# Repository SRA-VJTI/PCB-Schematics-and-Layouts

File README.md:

# PCB Schematics and Layouts
This Repository contains the schematic and layout files for all the PCBs designed at SRA for various competitions and workshops.

- **Robocon PCBs 2016**  
  PCB files made for the *Manually Operated Robot* in **Robocon 2016**.  
  Designed on **Autodesk EAGLE CAD**.  
  - **128 breakout**  
    - This is the breakout board for the *Atmega 128 Microcontroller* SMD Package.  
    - It also consists the External Clock Circuit and a connector slot for the programmer cable.  
  - **Main Board**  
    - The microcontroller breakout circuit is mounted on this pcb.  
    - It contains peripherals like input switches & LEDs, fuses for short-circuit protection and various connectors to connect sensors & actuators to the controller.  
    
- **Robocon PCBs 2017**  
  PCB files made for the *Manually Operated Robot* in **Robocon 2017**.  
  Designed on **Autodesk EAGLE CAD**.  
  - **128 breakout**  
    - This is the breakout board for the *Atmega 128 Microcontroller* SMD Package.  
    - It also consists the External Clock Circuit and a connector slot for the programmer cable.  
  - **Main Board**  
    - The microcontroller breakout circuit is mounted on this pcb.  
    - It contains peripherals like input switches & LEDs, fuses for short-circuit protection and various connectors to connect sensors & actuators to the controller.  
  - **Line Sensing Array**  
    - It contains a sensor array to detect different colors to help follow a line.  
  - **Power and Motor Control Breakout**  
    - It contains the circuit to connect several motor drivers to a single connector.  
    - It also has a Relay-based braking ciruit to pyhsically short the DC motor terminals.  
    - This PCB also contains the voltage regulators to power the microntroller circuits as well as the motor controllers.  

- **WallE 2016 Dev Brd**  
  - PCB files made for the **Line-follower Robot Workshop (WallE)** in the year 2016.  
  - It uses an **Atmega 16 Microcontroller** in its DIP package, with peripherals like input switches & LEDs, fuses for short-circuit protection, external clock circuit, programmer slot and various connectors to connect sensors & actuators to the controller.  
  - Designed on **KiCAD**.  

- **WallE 2.0 2017 Dev Brd**  
  - PCB files made for the **Line-follower and Self-Balancing Robot Workshop (WallE 2.0)** in the year 2017.  
  - Compared to the 2016 Dev Brd, this iteration has an extra slot to connect an MPU6050 inertial sensor.  
  - Designed on **Autodesk EAGLE CAD**.  

- **MPU Board**  
  - PCB files made for the **MPU 6050** inertial sensor breakout board, used in the **Self-balancing Robot Workshop (WallE 2.0)**.   
  - It has onboard *Pull-up resistors* for the *I2C protocol* lines (SCL and SDA).  
  - Connects to the main Dev Board through a 6 pin Flat Ribbon Cable.  
  - Designed on **Autodesk EAGLE CAD**.  

- **WallE 2.1 2018 Dev Brd**  
  - PCB files made for the **Line-follower and Self-Balancing Robot Workshop (WallE 2.1)** in the year 2018.  
  - It uses an **Espressif System's ESP32** SoC DevKit, with peripherals like input switches & LEDs, fuses for short-circuit protection, external clock circuit and various connectors to connect sensors & actuators to the controller.  
  - Designed on **Autodesk EAGLE CAD**.  

- **ESP 8266 Board**  
  - PCB files made for the **IOT Workshop** in the year 2016.  
  - It uses **Espressif System's ESP 8266** SoC.  
  - Contains a switch to toggle between flash mode and GPIO mode. 
  - Designed on **Autodesk EAGLE CAD**.

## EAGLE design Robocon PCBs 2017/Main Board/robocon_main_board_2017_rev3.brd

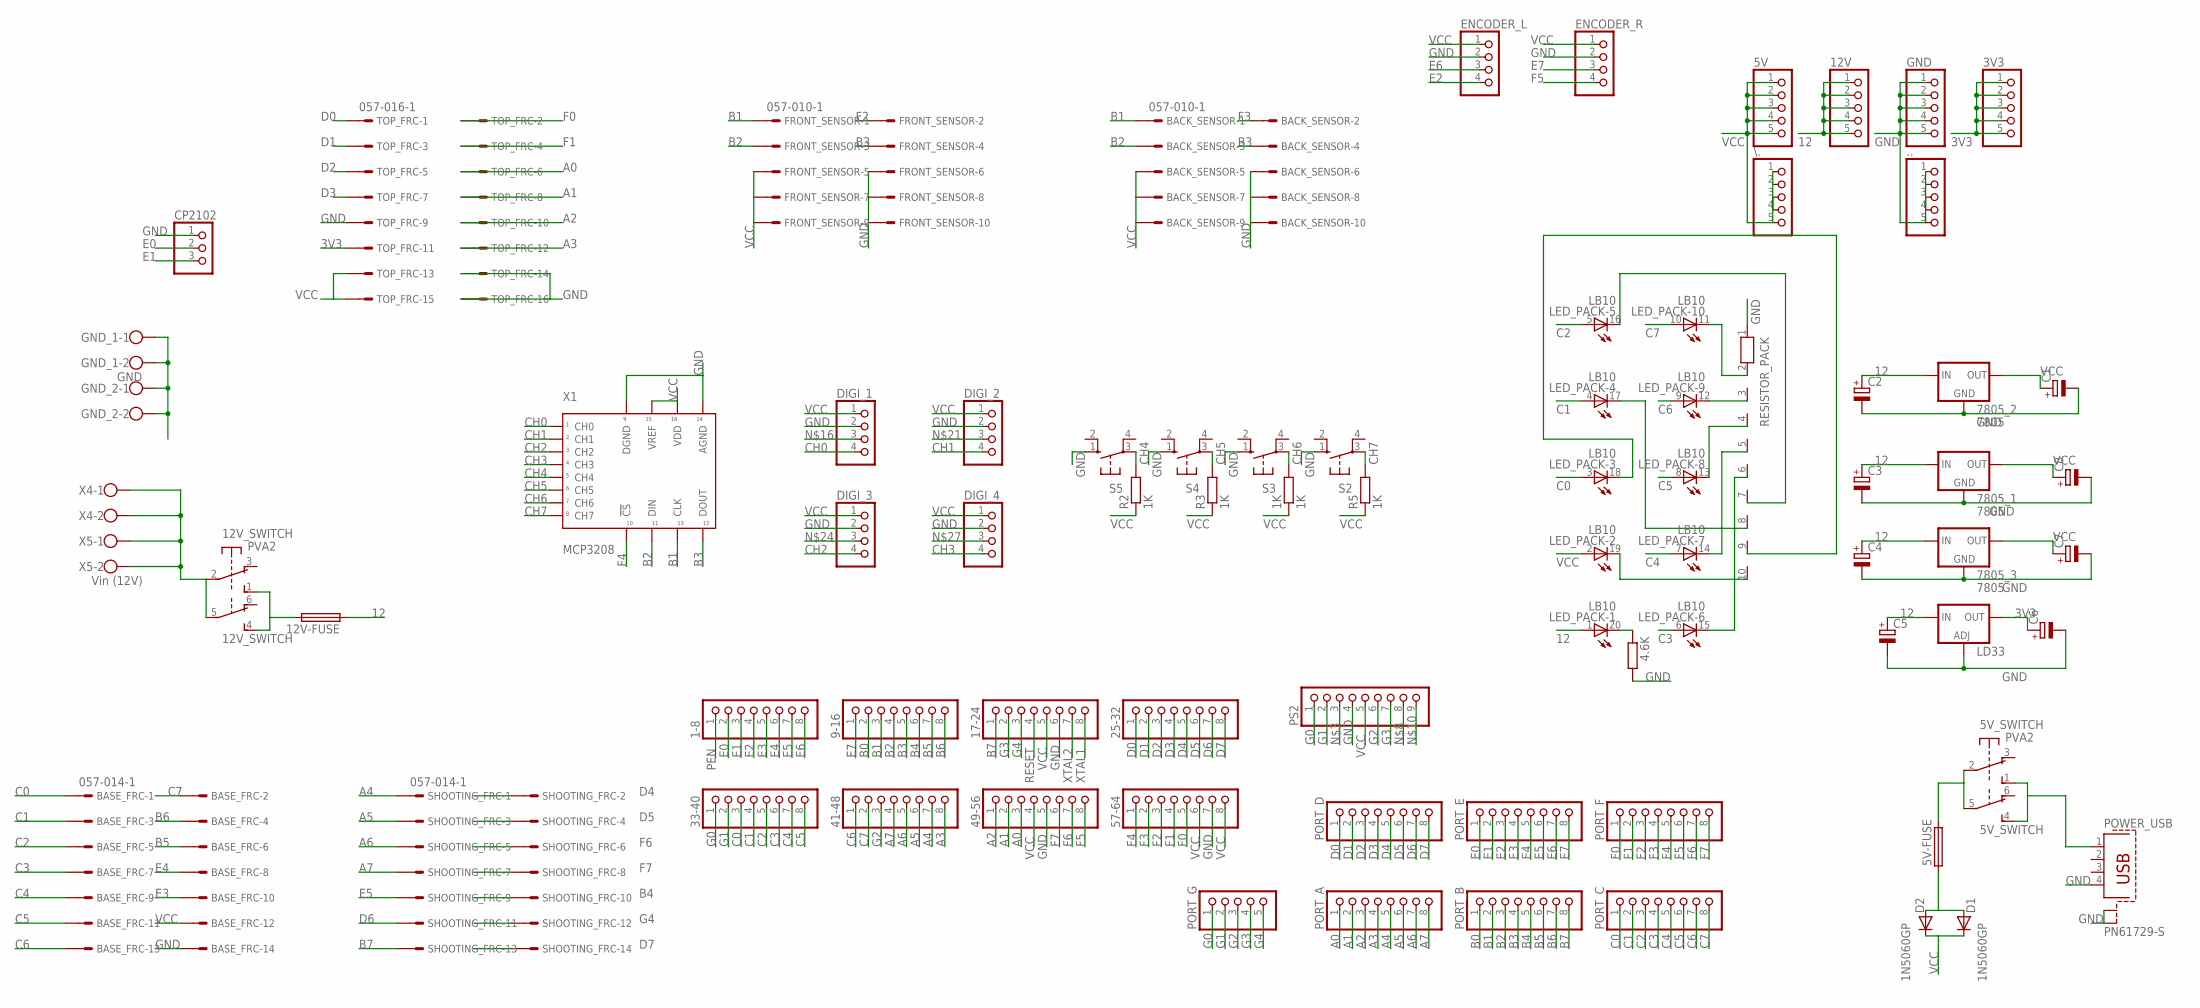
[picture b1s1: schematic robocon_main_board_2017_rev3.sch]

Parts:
1-8, 9-16, 17-24, 25-32, 33-40, 41-48, 49-56, 57-64: PINHD-1X8; 1X08
1K: 1K; 0204/7
3V3, 5V, 12V, ..: PINHD-1X5; 1X05
4.6K: R0204/7; 0204/7
5V-FUSE, 12V-FUSE: SH25
5V_SWITCH, 12V_SWITCH: PVA2; PVA2F
7805_1, 7805_2, 7805_3: 7805; 78XXS
BACK_SENSOR: 057-010-1
BASE_FRC: 057-014-1
C1, C2, C3, C4, C5, C6, C7, C8: CPOL-EUE2.5-5; E2,5-5
CP2102: PINHD-1X3; 1X03
D1, D2: 1N5060GP; DO15-12
DIGI_1, DIGI_2, DIGI_3, DIGI_4: PINHD-1X4; 1X04
ENCODER_L: PINHD-1X4; 1X04
ENCODER_R: PINHD-1X4; 1X04
FRONT_SENSOR: 057-010-1
GND: PINHD-1X5; 1X05
GND_1: GND; W237-102
GND_2: W237-102
LD33: LM317TS; 317TS
LED_PACK: LB10
PORT_A: PINHD-1X8; 1X08
PORT_B: PINHD-1X8; 1X08
PORT_C: PINHD-1X8; 1X08
PORT_D: PINHD-1X8; 1X08
PORT_E: PINHD-1X8; 1X08
PORT_F: PINHD-1X8; 1X08
PORT_G: PINHD-1X5; 1X05
POWER_USB: PN61729-S
PS2: PINHD-1X9; 1X09
R2, R3, R5: 1K; 0204/7
RESISTOR_PACK: RN09; RN-10
S2, S3, S4, S5: 10-XX; B3F-10XX
SHOOTING_FRC: 057-014-1
TOP_FRC: 057-016-1
X1: MCP3208; DIP16
X4: W237-102
X5: Vin (12V); W237-102
\.: PINHD-1X5; 1X05

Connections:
3V3: 3V3.1, 3V3.2, 3V3.3, 3V3.4, 3V3.5, C6.+, LD33.2 (OUT), TOP_FRC.11
12: 12V.1, 12V.2, 12V.3, 12V.4, 12V.5, 12V-FUSE.1, 7805_1.IN, 7805_2.IN, 7805_3.IN, C2.+, C3.+, C4.+, C5.+, LD33.3 (IN), LED_PACK.1 (A)
A0: 49-56.3, PORT_A.1, TOP_FRC.6
A1: 49-56.2, PORT_A.2, TOP_FRC.8
A2: 49-56.1, PORT_A.3, TOP_FRC.10
A3: 41-48.8, PORT_A.4, TOP_FRC.12
A4: 41-48.7, PORT_A.5, SHOOTING_FRC.1
A5: 41-48.6, PORT_A.6, SHOOTING_FRC.3
A6: 41-48.5, PORT_A.7, SHOOTING_FRC.5
A7: 41-48.4, PORT_A.8, SHOOTING_FRC.7
B0: 9-16.2, PORT_B.1
B1: 9-16.3, BACK_SENSOR.1, FRONT_SENSOR.1, PORT_B.2, X1.P$13 (CLK)
B2: 9-16.4, BACK_SENSOR.3, FRONT_SENSOR.3, PORT_B.3, X1.P$11 (DIN)
B3: 9-16.5, BACK_SENSOR.4, FRONT_SENSOR.4, PORT_B.4, X1.P$12 (DOUT)
B4: 9-16.6, PORT_B.5, SHOOTING_FRC.10
B5: 9-16.7, BASE_FRC.6, PORT_B.6
B6: 9-16.8, BASE_FRC.4, PORT_B.7
B7: 17-24.1, PORT_B.8, SHOOTING_FRC.13
C0: 33-40.3, BASE_FRC.1, LED_PACK.3 (A), PORT_C.1
C1: 33-40.4, BASE_FRC.3, LED_PACK.4 (A), PORT_C.2
C2: 33-40.5, BASE_FRC.5, LED_PACK.5 (A), PORT_C.3
C3: 33-40.6, BASE_FRC.7, LED_PACK.6 (A), PORT_C.4
C4: 33-40.7, BASE_FRC.9, LED_PACK.7 (A), PORT_C.5
C5: 33-40.8, BASE_FRC.11, LED_PACK.8 (A), PORT_C.6
C6: 41-48.1, BASE_FRC.13, LED_PACK.9 (A), PORT_C.7
C7: 41-48.2, BASE_FRC.2, LED_PACK.10 (A), PORT_C.8
CH0: DIGI_1.4, X1.P$1 (CH0)
CH1: DIGI_2.4, X1.P$2 (CH1)
CH2: DIGI_3.4, X1.P$3 (CH2)
CH3: DIGI_4.4, X1.P$4 (CH3)
CH4: R2.2, S5.3, X1.P$5 (CH4)
CH5: R3.2, S4.3, X1.P$6 (CH5)
CH6: 1K.2, S3.3, X1.P$7 (CH6)
CH7: R5.2, S2.3, X1.P$8 (CH7)
D0: 25-32.1, PORT_D.1, TOP_FRC.1
D1: 25-32.2, PORT_D.2, TOP_FRC.3
D2: 25-32.3, PORT_D.3, TOP_FRC.5
D3: 25-32.4, PORT_D.4, TOP_FRC.7
D4: 25-32.5, PORT_D.5, SHOOTING_FRC.2
D5: 25-32.6, PORT_D.6, SHOOTING_FRC.4
D6: 25-32.7, PORT_D.7, SHOOTING_FRC.11
D7: 25-32.8, PORT_D.8, SHOOTING_FRC.14
E0: 1-8.2, CP2102.2, PORT_E.1
E1: 1-8.3, CP2102.3, PORT_E.2
E2: 1-8.4, ENCODER_L.4, PORT_E.3
E3: 1-8.5, BASE_FRC.10, PORT_E.4
E4: 1-8.6, BASE_FRC.8, PORT_E.5
E5: 1-8.7, PORT_E.6, SHOOTING_FRC.9
E6: 1-8.8, ENCODER_L.3, PORT_E.7
E7: 9-16.1, ENCODER_R.3, PORT_E.8
F0: 57-64.5, PORT_F.1, TOP_FRC.2
F1: 57-64.4, PORT_F.2, TOP_FRC.4
F2: 57-64.3, FRONT_SENSOR.2, PORT_F.3
F3: 57-64.2, BACK_SENSOR.2, PORT_F.4
F4: 57-64.1, PORT_F.5, X1.P$10 (!CS)
F5: 49-56.8, ENCODER_R.4, PORT_F.6
F6: 49-56.7, PORT_F.7, SHOOTING_FRC.6
F7: 49-56.6, PORT_F.8, SHOOTING_FRC.8
G0: 33-40.1, PORT_G.1, PS2.1
G1: 33-40.2, PORT_G.2, PS2.2
G2: 41-48.3, PORT_G.3, PS2.6
G3: 17-24.2, PORT_G.4, PS2.7
G4: 17-24.3, PORT_G.5, SHOOTING_FRC.12
GND: 4.6K.2, 17-24.6, 49-56.5, 57-64.7, 7805_1.GND, 7805_2.GND, 7805_3.GND, ...1, ...2, ...3, ...4, ...5, BACK_SENSOR.6, BACK_SENSOR.8, BACK_SENSOR.10, BASE_FRC.14, C1.-, C2.-, C3.-, C4.-, C5.-, C6.-, C7.-, C8.-, CP2102.1, DIGI_1.2, DIGI_2.2, DIGI_3.2, DIGI_4.2, ENCODER_L.2, ENCODER_R.2, FRONT_SENSOR.6, FRONT_SENSOR.8, FRONT_SENSOR.10, GND.1, GND.2, GND.3, GND.4, GND.5, GND_1.1, GND_1.2, GND_2.1, GND_2.2, LD33.1 (ADJ), POWER_USB.4, POWER_USB.S1, POWER_USB.S2, PS2.4, RESISTOR_PACK.1, S2.1 (S), S3.1 (S), S4.1 (S), S5.1 (S), TOP_FRC.9, TOP_FRC.14, TOP_FRC.16, X1.P$9 (DGND), X1.P$14 (AGND)
unnamed: LED_PACK.11 (C), RESISTOR_PACK.2
unnamed: LED_PACK.12 (C), RESISTOR_PACK.3
unnamed: LED_PACK.13 (C), RESISTOR_PACK.4
unnamed: LED_PACK.14 (C), RESISTOR_PACK.5
unnamed: LED_PACK.15 (C), RESISTOR_PACK.6
unnamed: LED_PACK.16 (C), RESISTOR_PACK.7
unnamed: LED_PACK.17 (C), RESISTOR_PACK.8
unnamed: LED_PACK.18 (C), RESISTOR_PACK.9
unnamed: LED_PACK.19 (C), RESISTOR_PACK.10
unnamed: 4.6K.1, LED_PACK.20 (C)
unnamed: 5V_SWITCH.1 (S), 5V_SWITCH.4 (S), POWER_USB.1
unnamed: 5V-FUSE.2, 5V_SWITCH.2, 5V_SWITCH.5
unnamed: 12V_SWITCH.2, 12V_SWITCH.5, X4.1, X4.2, X5.1, X5.2
unnamed: 12V-FUSE.2, 12V_SWITCH.1 (S), 12V_SWITCH.4 (S)
unnamed: 5V-FUSE.1, D1.A, D2.A
PEN: 1-8.1
RESET: 17-24.4
VCC: 1K.1, 5V.1, 5V.2, 5V.3, 5V.4, 5V.5, 17-24.5, 49-56.4, 57-64.6, 57-64.8, 7805_1.OUT, 7805_2.OUT, 7805_3.OUT, BACK_SENSOR.5, BACK_SENSOR.7, BACK_SENSOR.9, BASE_FRC.12, C1.+, C7.+, C8.+, D1.C, D2.C, DIGI_1.1, DIGI_2.1, DIGI_3.1, DIGI_4.1, ENCODER_L.1, ENCODER_R.1, FRONT_SENSOR.5, FRONT_SENSOR.7, FRONT_SENSOR.9, LED_PACK.2 (A), PS2.5, R2.1, R3.1, R5.1, TOP_FRC.13, TOP_FRC.15, X1.P$15 (VREF), X1.P$16 (VDD), \..1, \..2, \..3, \..4, \..5
XTAL1: 17-24.8
XTAL2: 17-24.7

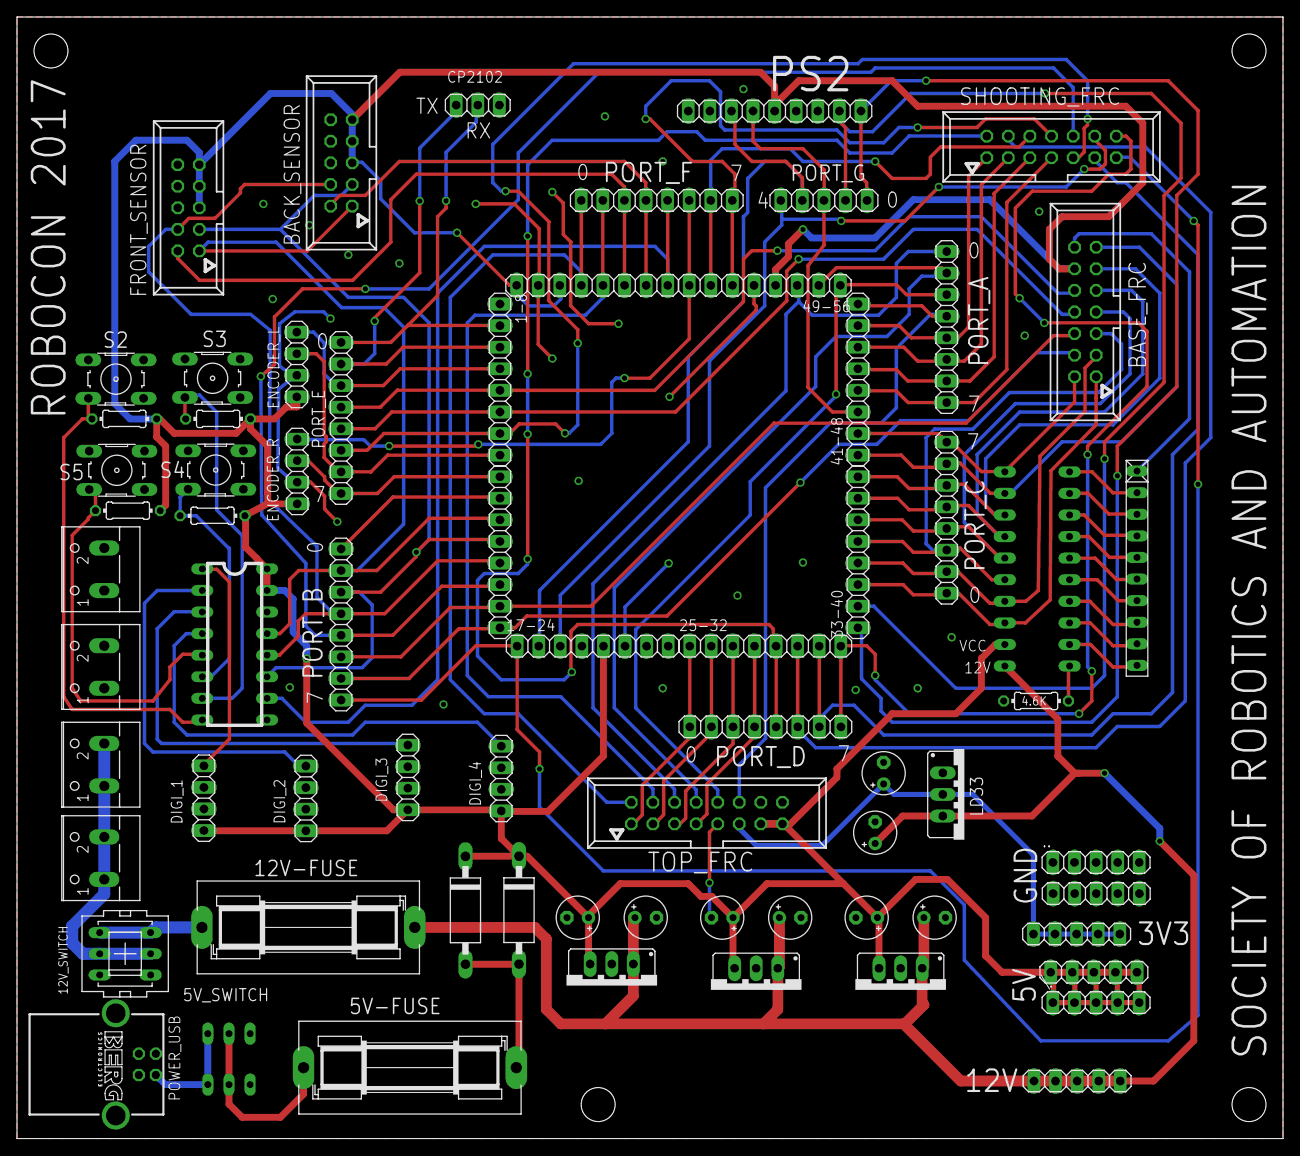
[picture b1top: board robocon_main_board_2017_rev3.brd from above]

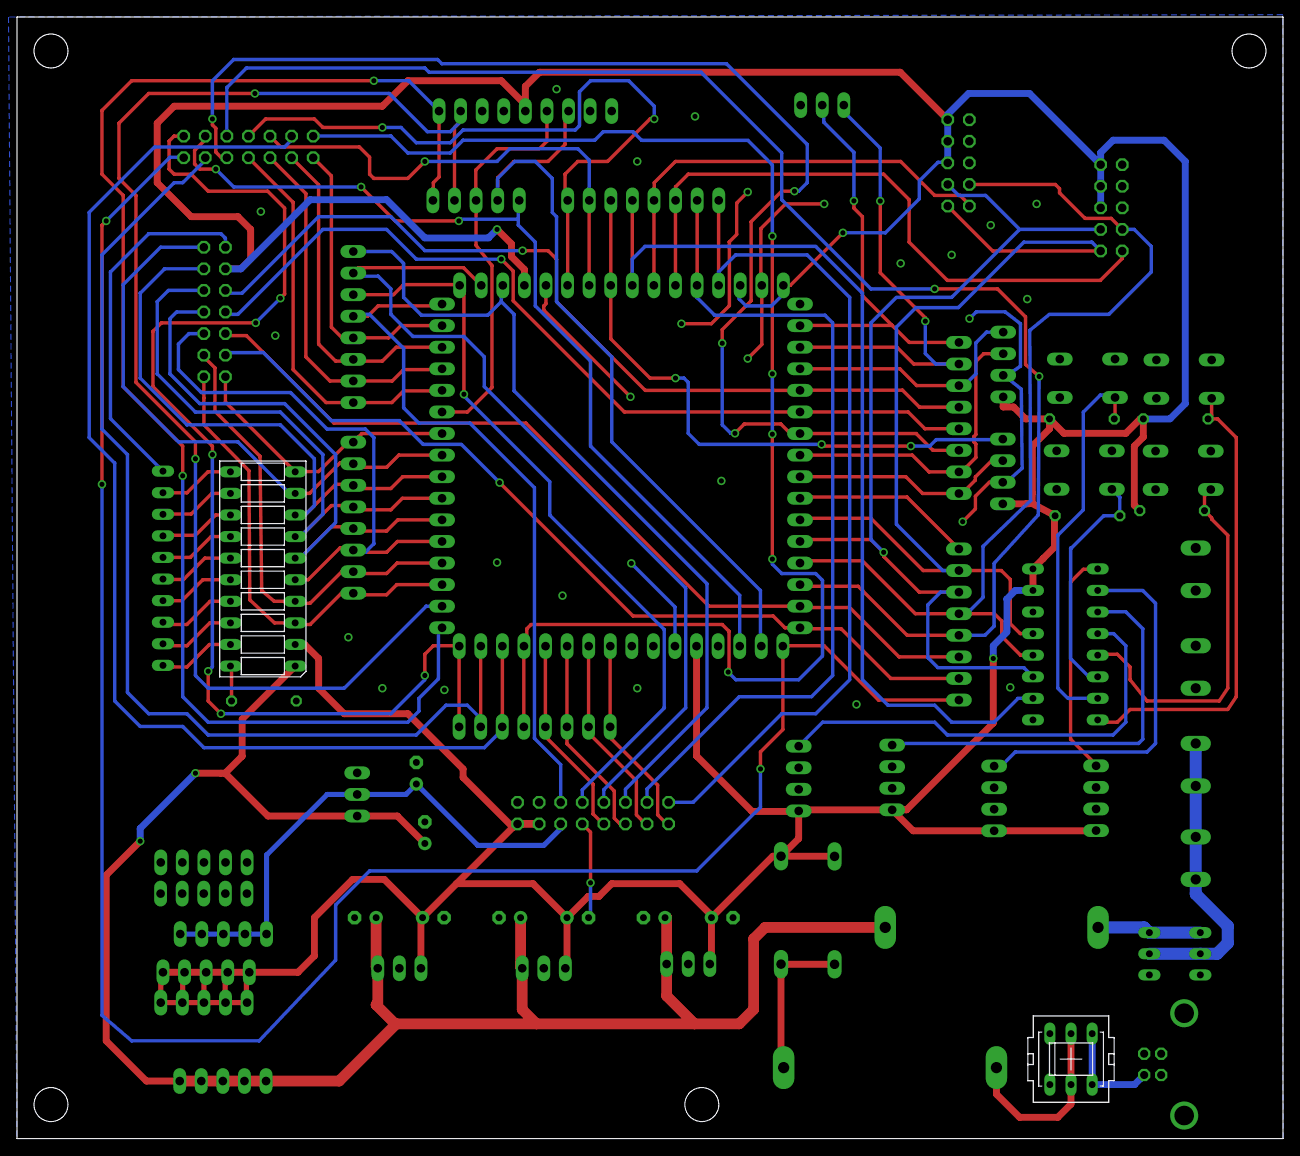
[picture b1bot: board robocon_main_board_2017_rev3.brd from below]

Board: 2 copper layers, 149.0 x 132.0 mm, 69 parts (2 on the bottom side), 80 nets.

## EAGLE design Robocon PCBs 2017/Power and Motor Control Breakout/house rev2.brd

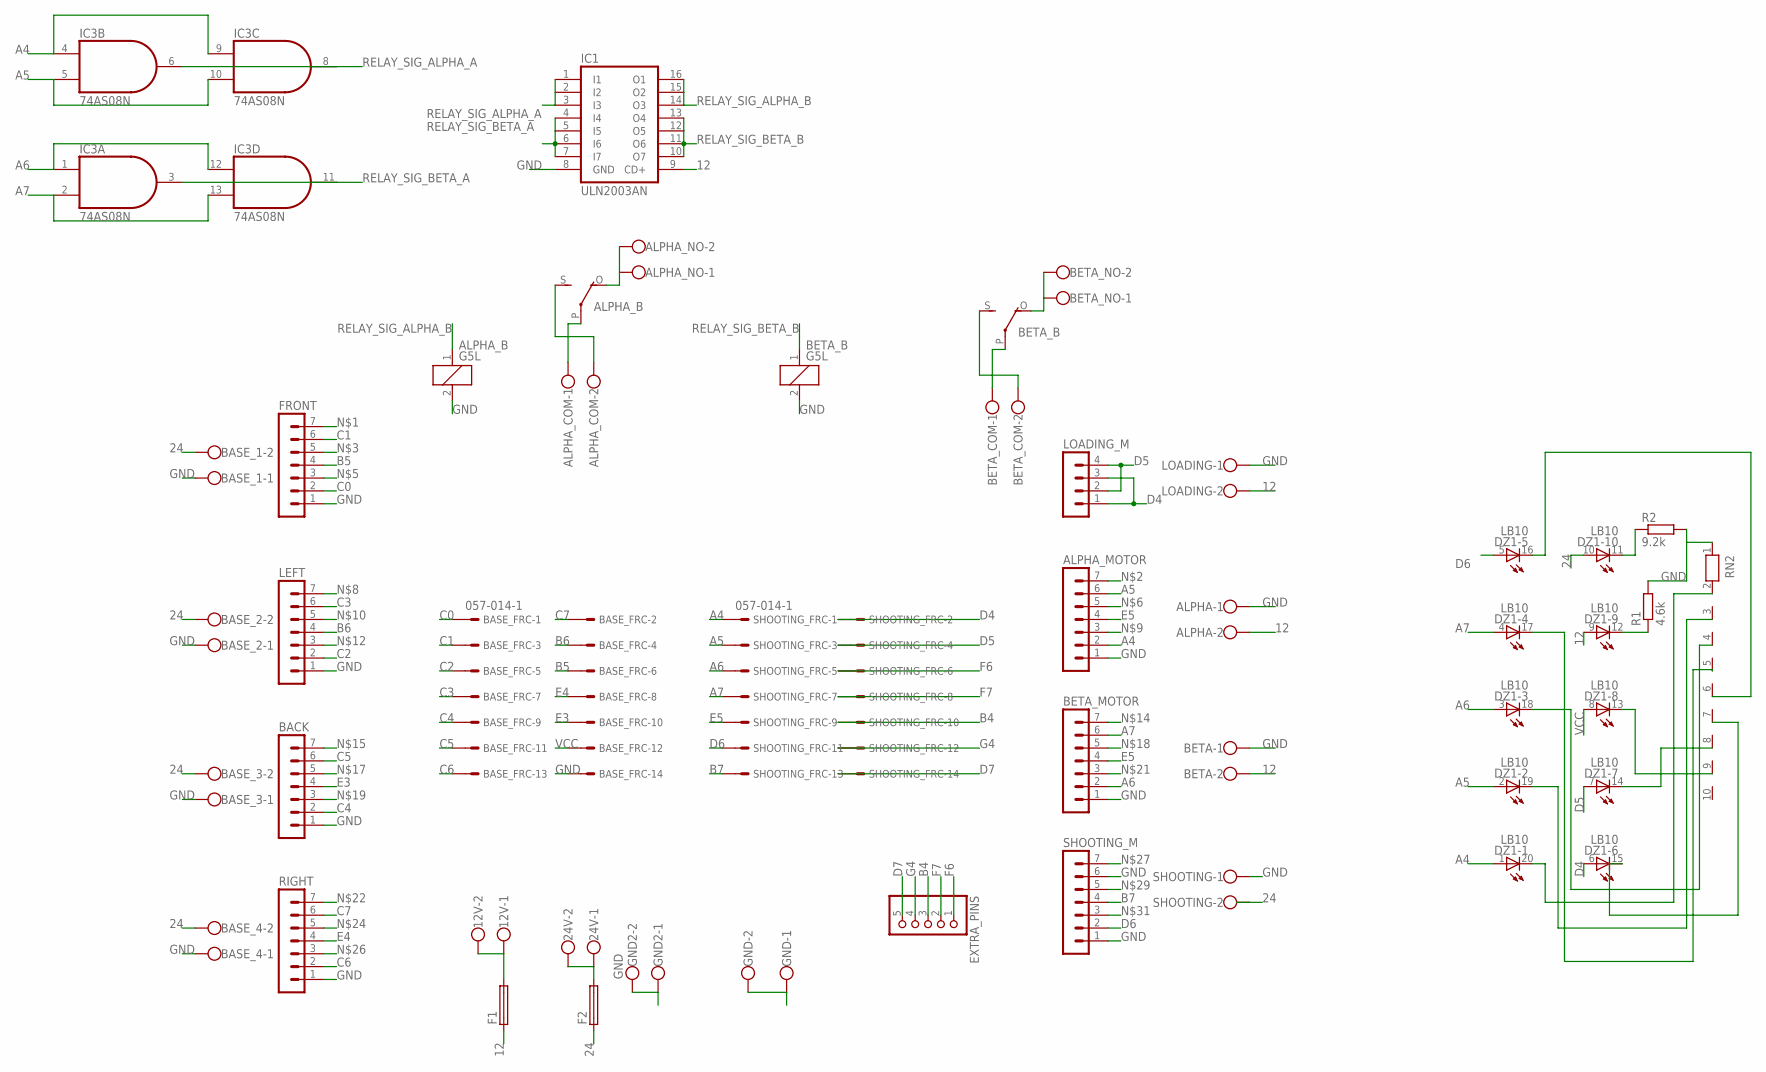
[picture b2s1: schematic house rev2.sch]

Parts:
12V, 24V: W237-102
ALPHA: W237-102
ALPHA_B: G5L; G5LE
ALPHA_COM: W237-102
ALPHA_MOTOR: MA07-1
ALPHA_NO: W237-102
BACK: MA07-1
BASE_1, BASE_2, BASE_3, BASE_4: W237-102
BASE_FRC: 057-014-1
BETA: W237-102
BETA_B: G5L; G5LE
BETA_COM: W237-102
BETA_MOTOR: MA07-1
BETA_NO: W237-102
DZ1: LB10
EXTRA_PINS: PINHD-1X5; 1X05
F1, F2: SH25
FRONT: MA07-1
GND: W237-102
GND2: GND; W237-102
IC1: ULN2003AN; DIL16
IC3: 74AS08N; DIL14
LEFT: MA07-1
LOADING: W237-102
LOADING_M: MA04-1
R1: 4.6k; 0204/7
R2: 9.2k; 0204/7
RIGHT: MA07-1
RN2: RN09; RN-10
SHOOTING: W237-102
SHOOTING_FRC: 057-014-1
SHOOTING_M: MA07-1

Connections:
12: ALPHA.2, BETA.2, DZ1.9 (A), F1.1, IC1.9 (CD+), LOADING.2
24: BASE_1.2, BASE_2.2, BASE_3.2, BASE_4.2, DZ1.10 (A), F2.1, SHOOTING.2
A4: ALPHA_MOTOR.2, DZ1.1 (A), IC3.4 (I0), IC3.9 (I0), SHOOTING_FRC.1
A5: ALPHA_MOTOR.6, DZ1.2 (A), IC3.5 (I1), IC3.10 (I1), SHOOTING_FRC.3
A6: BETA_MOTOR.2, DZ1.3 (A), IC3.1 (I0), IC3.12 (I0), SHOOTING_FRC.5
A7: BETA_MOTOR.6, DZ1.4 (A), IC3.2 (I1), IC3.13 (I1), SHOOTING_FRC.7
B4: EXTRA_PINS.3, SHOOTING_FRC.10
B5: BASE_FRC.6, FRONT.4
B6: BASE_FRC.4, LEFT.4
B7: SHOOTING_FRC.13, SHOOTING_M.4
C0: BASE_FRC.1, FRONT.2
C1: BASE_FRC.3, FRONT.6
C2: BASE_FRC.5, LEFT.2
C3: BASE_FRC.7, LEFT.6
C4: BACK.2, BASE_FRC.9
C5: BACK.6, BASE_FRC.11
C6: BASE_FRC.13, RIGHT.2
C7: BASE_FRC.2, RIGHT.6
D4: DZ1.6 (A), LOADING_M.1, LOADING_M.3, SHOOTING_FRC.2
D5: DZ1.7 (A), LOADING_M.2, LOADING_M.4, SHOOTING_FRC.4
D6: DZ1.5 (A), SHOOTING_FRC.11, SHOOTING_M.2
D7: EXTRA_PINS.5, SHOOTING_FRC.14
E3: BACK.4, BASE_FRC.10
E4: BASE_FRC.8, RIGHT.4
E5: ALPHA_MOTOR.4, BETA_MOTOR.4, SHOOTING_FRC.9
F6: EXTRA_PINS.1, SHOOTING_FRC.6
F7: EXTRA_PINS.2, SHOOTING_FRC.8
G4: EXTRA_PINS.4, SHOOTING_FRC.12
GND: ALPHA.1, ALPHA_B.2, ALPHA_MOTOR.1, BACK.1, BASE_1.1, BASE_2.1, BASE_3.1, BASE_4.1, BASE_FRC.14, BETA.1, BETA_B.2, BETA_MOTOR.1, FRONT.1, GND.1, GND.2, GND2.1, GND2.2, IC1.8 (GND), IC3.7 (GND), LEFT.1, LOADING.1, R1.2, R2.2, RIGHT.1, RN2.1, SHOOTING.1, SHOOTING_M.1, SHOOTING_M.6
unnamed: DZ1.20 (C), RN2.2
unnamed: DZ1.19 (C), RN2.3
unnamed: DZ1.18 (C), RN2.4
unnamed: DZ1.17 (C), RN2.5
unnamed: DZ1.16 (C), RN2.6
unnamed: DZ1.15 (C), RN2.7
unnamed: BETA_B.P, BETA_COM.1
unnamed: DZ1.14 (C), RN2.8
unnamed: DZ1.13 (C), RN2.9
unnamed: DZ1.12 (C), R1.1
unnamed: DZ1.11 (C), R2.1
unnamed: BETA_B.S, BETA_COM.2
unnamed: ALPHA_B.S, ALPHA_COM.2
unnamed: ALPHA_B.P, ALPHA_COM.1
unnamed: ALPHA_B.O, ALPHA_NO.1, ALPHA_NO.2
unnamed: BETA_B.O, BETA_NO.1, BETA_NO.2
unnamed: 24V.1, 24V.2, F2.2
unnamed: 12V.1, 12V.2, F1.2
RELAY_SIG_ALPHA_A: IC1.1 (I1), IC1.2 (I2), IC1.3 (I3), IC3.6 (O), IC3.8 (O)
RELAY_SIG_ALPHA_B: ALPHA_B.1, IC1.14 (O3), IC1.15 (O2), IC1.16 (O1)
RELAY_SIG_BETA_A: IC1.4 (I4), IC1.5 (I5), IC1.6 (I6), IC1.7 (I7), IC3.3 (O), IC3.11 (O)
RELAY_SIG_BETA_B: BETA_B.1, IC1.10 (O7), IC1.11 (O6), IC1.12 (O5), IC1.13 (O4)
VCC: BASE_FRC.12, DZ1.8 (A), IC3.14 (VCC)

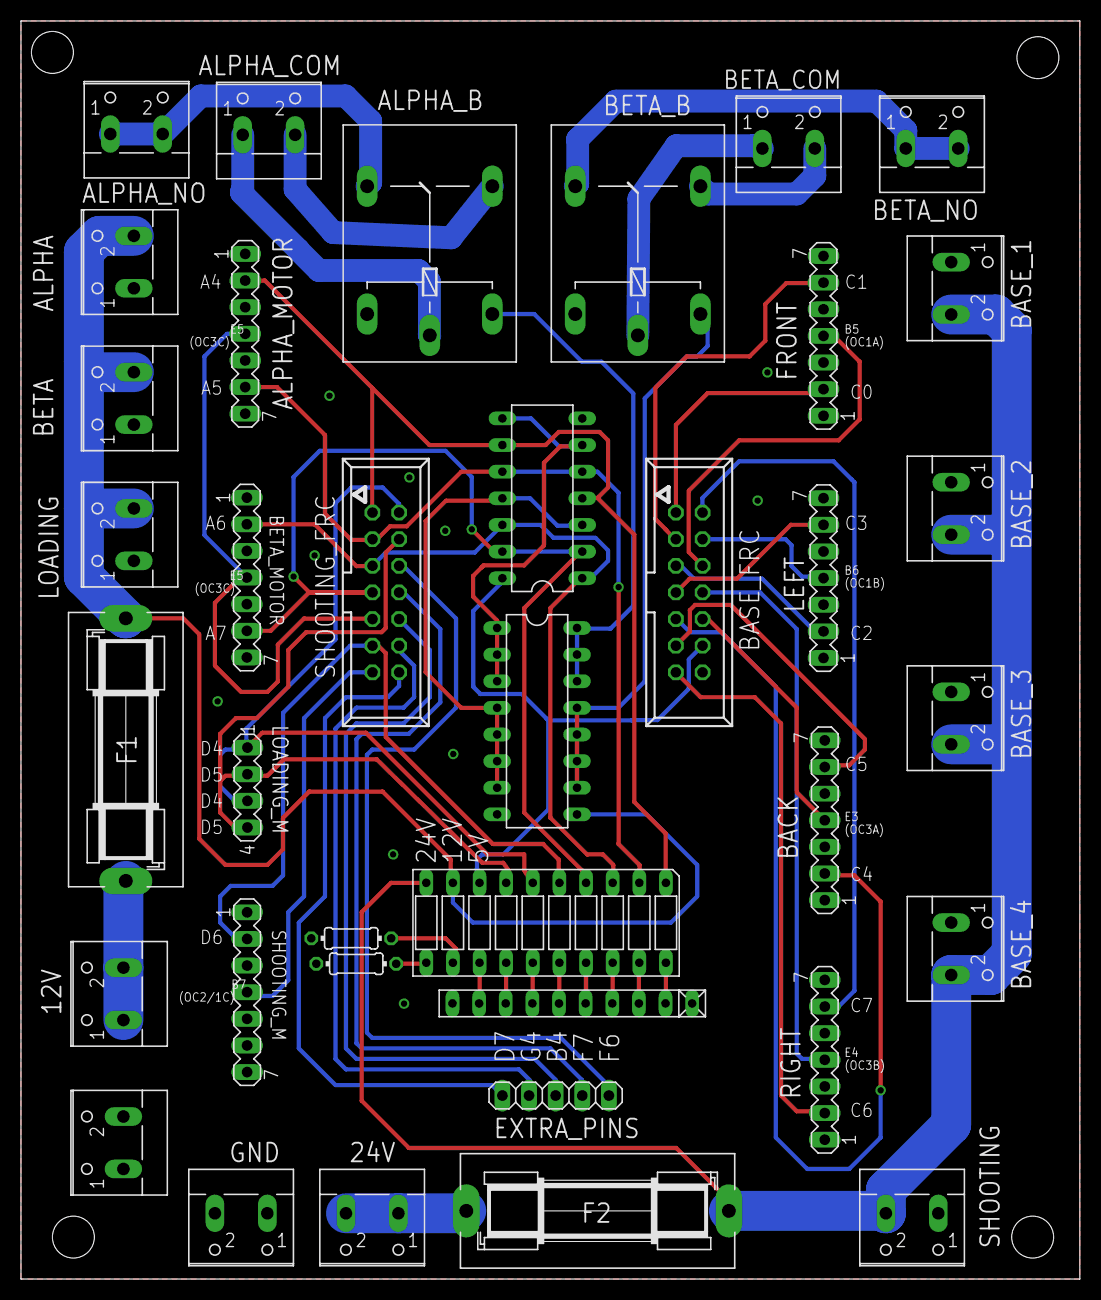
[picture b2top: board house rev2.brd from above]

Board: 2 copper layers, 101.0 x 120.0 mm, 37 parts (0 on the bottom side), 52 nets.

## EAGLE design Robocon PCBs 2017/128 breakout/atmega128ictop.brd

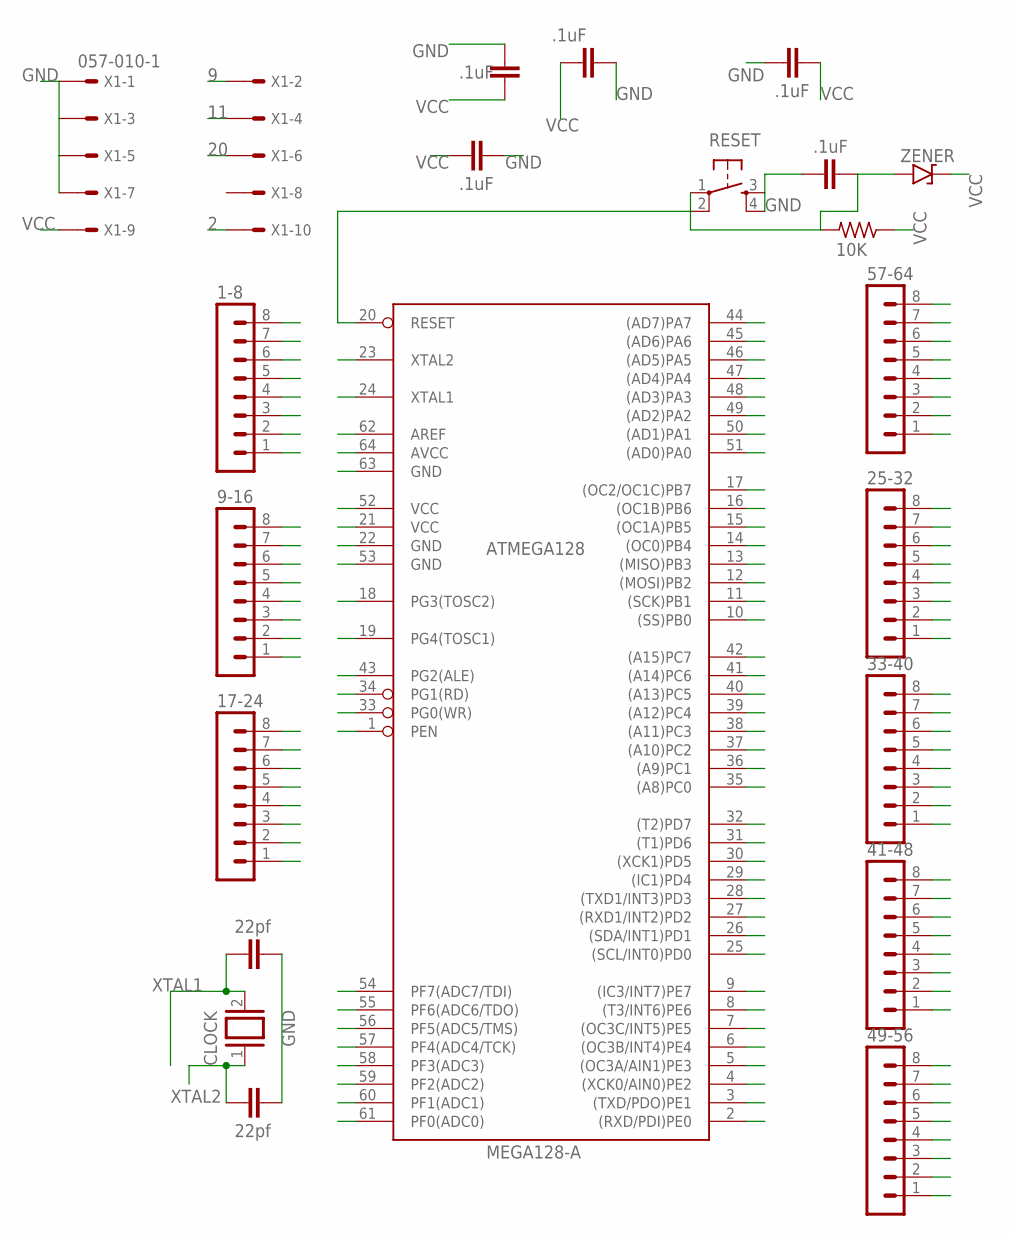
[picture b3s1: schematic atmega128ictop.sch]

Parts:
1-8, 9-16, 17-24, 25-32, 33-40, 41-48, 49-56, 57-64: MA08-1
ATMEGA128: MEGA128-A; TQFP64
C1, C2, C5, C6, C7: .1uF; C5B2.5
C3, C4: 22pf; C5B2.5
CLOCK: XTAL/S; QS
D1: ZENER; DO35-2
R1: 10K; 0204/5
RESET: DTS-6
X1: 057-010-1

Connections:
1: 1-8.1, ATMEGA128.1 (PEN)
2: 1-8.2, ATMEGA128.2 ((RXD/PDI)PE0), X1.10
3: 1-8.3, ATMEGA128.3 ((TXD/PDO)PE1)
4: 1-8.4, ATMEGA128.4 ((XCK0/AIN0)PE2)
5: 1-8.5, ATMEGA128.5 ((OC3A/AIN1)PE3)
6: 1-8.6, ATMEGA128.6 ((OC3B/INT4)PE4)
7: 1-8.7, ATMEGA128.7 ((OC3C/INT5)PE5)
8: 1-8.8, ATMEGA128.8 ((T3/INT6)PE6)
9: 9-16.1, ATMEGA128.9 ((IC3/INT7)PE7), X1.2
10: 9-16.2, ATMEGA128.10 ((SS)PB0)
11: 9-16.3, ATMEGA128.11 ((SCK)PB1), X1.4
12: 9-16.4, ATMEGA128.12 ((MOSI)PB2)
13: 9-16.5, ATMEGA128.13 ((MISO)PB3)
14: 9-16.6, ATMEGA128.14 ((OC0)PB4)
15: 9-16.7, ATMEGA128.15 ((OC1A)PB5)
16: 9-16.8, ATMEGA128.16 ((OC1B)PB6)
17: 17-24.1, ATMEGA128.17 ((OC2/OC1C)PB7)
18: 17-24.2, ATMEGA128.18 (PG3(TOSC2))
19: 17-24.3, ATMEGA128.19 (PG4(TOSC1))
20: 17-24.4, ATMEGA128.20 (RESET), C5.1, D1.A, R1.2, RESET.1, RESET.2, X1.6
25: 25-32.1, ATMEGA128.25 ((SCL/INT0)PD0)
26: 25-32.2, ATMEGA128.26 ((SDA/INT1)PD1)
27: 25-32.3, ATMEGA128.27 ((RXD1/INT2)PD2)
28: 25-32.4, ATMEGA128.28 ((TXD1/INT3)PD3)
29: 25-32.5, ATMEGA128.29 ((IC1)PD4)
30: 25-32.6, ATMEGA128.30 ((XCK1)PD5)
31: 25-32.7, ATMEGA128.31 ((T1)PD6)
32: 25-32.8, ATMEGA128.32 ((T2)PD7)
33: 33-40.1, ATMEGA128.33 (PG0(WR))
34: 33-40.2, ATMEGA128.34 (PG1(RD))
35: 33-40.3, ATMEGA128.35 ((A8)PC0)
36: 33-40.4, ATMEGA128.36 ((A9)PC1)
37: 33-40.5, ATMEGA128.37 ((A10)PC2)
38: 33-40.6, ATMEGA128.38 ((A11)PC3)
39: 33-40.7, ATMEGA128.39 ((A12)PC4)
40: 33-40.8, ATMEGA128.40 ((A13)PC5)
41: 41-48.1, ATMEGA128.41 ((A14)PC6)
42: 41-48.2, ATMEGA128.42 ((A15)PC7)
43: 41-48.3, ATMEGA128.43 (PG2(ALE))
44: 41-48.4, ATMEGA128.44 ((AD7)PA7)
45: 41-48.5, ATMEGA128.45 ((AD6)PA6)
46: 41-48.6, ATMEGA128.46 ((AD5)PA5)
47: 41-48.7, ATMEGA128.47 ((AD4)PA4)
48: 41-48.8, ATMEGA128.48 ((AD3)PA3)
49: 49-56.1, ATMEGA128.49 ((AD2)PA2)
50: 49-56.2, ATMEGA128.50 ((AD1)PA1)
51: 49-56.3, ATMEGA128.51 ((AD0)PA0)
54: 49-56.6, ATMEGA128.54 (PF7(ADC7/TDI))
55: 49-56.7, ATMEGA128.55 (PF6(ADC6/TDO))
56: 49-56.8, ATMEGA128.56 (PF5(ADC5/TMS))
57: 57-64.1, ATMEGA128.57 (PF4(ADC4/TCK))
58: 57-64.2, ATMEGA128.58 (PF3(ADC3))
59: 57-64.3, ATMEGA128.59 (PF2(ADC2))
60: 57-64.4, ATMEGA128.60 (PF1(ADC1))
61: 57-64.5, ATMEGA128.61 (PF0(ADC0))
62: 57-64.6
GND: 17-24.6, 49-56.5, 57-64.7, ATMEGA128.22 (GND), ATMEGA128.53 (GND), ATMEGA128.63 (GND), C1.1, C2.2, C3.2, C4.2, C5.2, C6.2, C7.2, RESET.3, RESET.4, X1.1, X1.3, X1.5, X1.7
VCC: 17-24.5, 49-56.4, 57-64.8, ATMEGA128.21 (VCC), ATMEGA128.52 (VCC), ATMEGA128.62 (AREF), ATMEGA128.64 (AVCC), C1.2, C2.1, C6.1, C7.1, D1.C, R1.1, X1.9
XTAL1: 17-24.8, ATMEGA128.24 (XTAL1), C3.1, CLOCK.2
XTAL2: 17-24.7, ATMEGA128.23 (XTAL2), C4.1, CLOCK.1

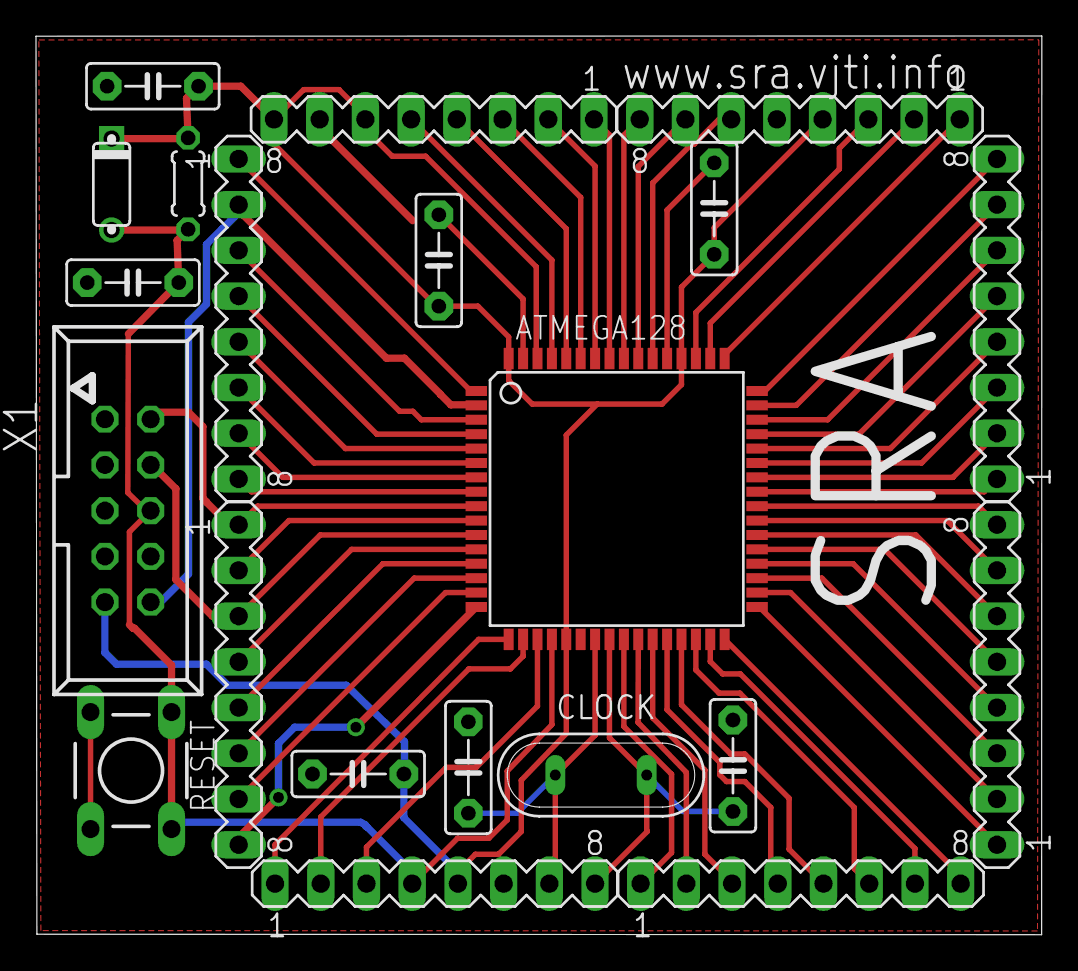
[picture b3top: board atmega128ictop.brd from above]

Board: 2 copper layers, 55.9 x 49.9 mm, 21 parts (0 on the bottom side), 59 nets.

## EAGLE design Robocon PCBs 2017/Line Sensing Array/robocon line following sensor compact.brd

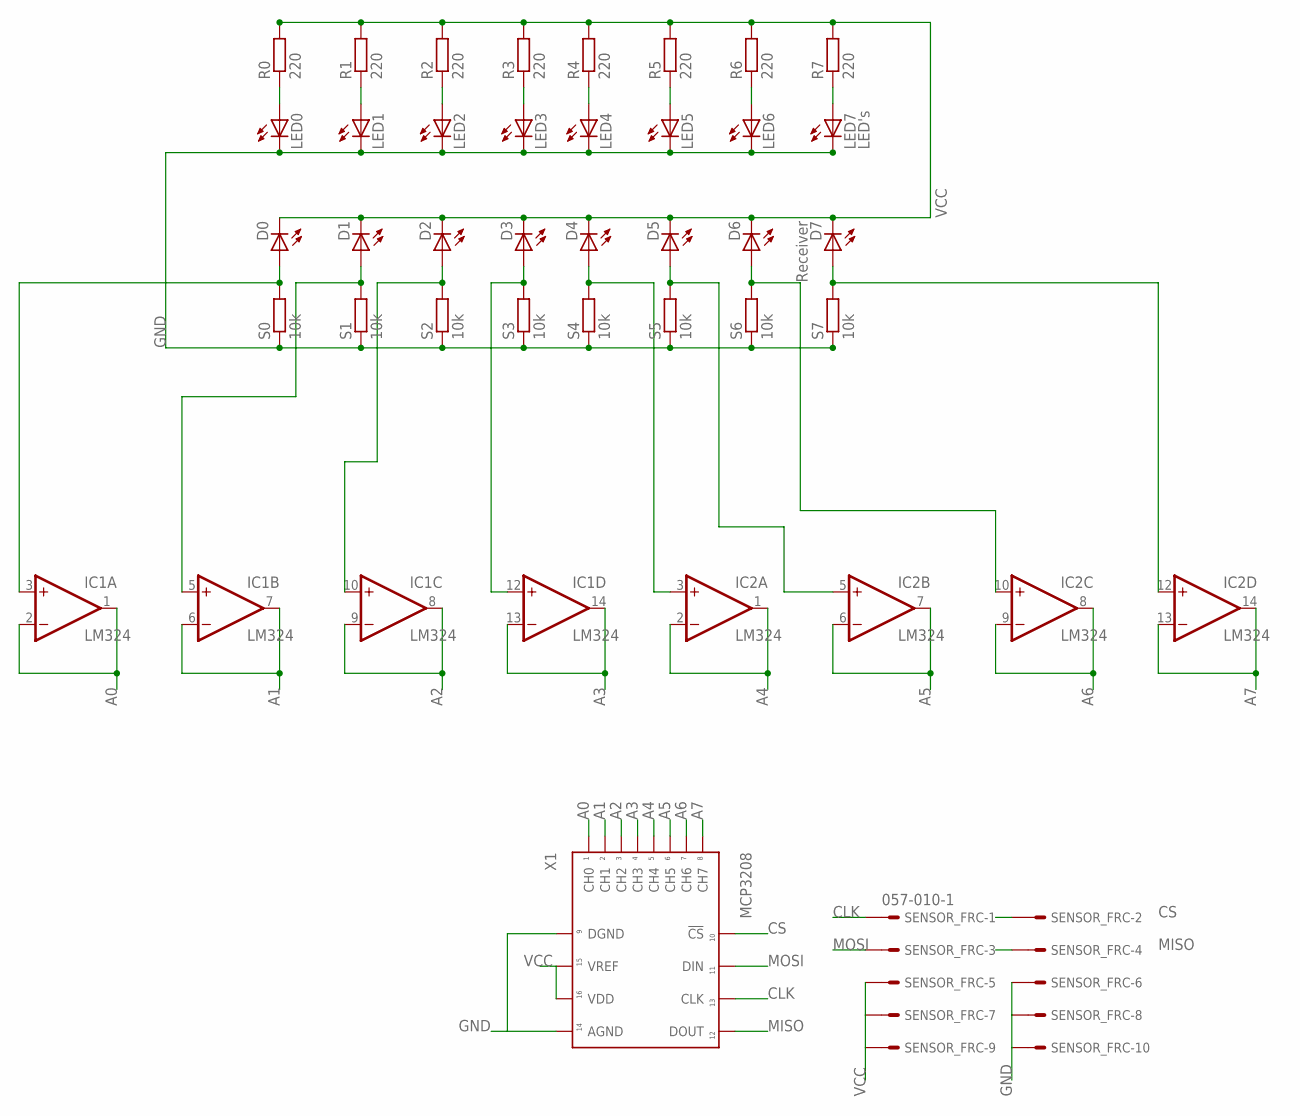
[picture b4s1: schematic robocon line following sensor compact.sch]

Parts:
D0, D1, D2, D3, D4, D5, D6: LED5MM
D7: Receiver; LED5MM
IC1, IC2: LM324; DIL14
LED0, LED1, LED2, LED3, LED4, LED5, LED6: LED5MM
LED7: LED's; LED5MM
R0, R1, R2, R3, R4, R5, R6, R7: 220; 0207/10
S0, S1, S2, S3, S4, S5, S6, S7: 10k; 0207/10
SENSOR_FRC: 057-010-1
X1: MCP3208; DIP16

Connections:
A0: IC1.1 (OUT), IC1.2 (-IN), X1.P$1 (CH0)
A1: IC1.6 (-IN), IC1.7 (OUT), X1.P$2 (CH1)
A2: IC1.8 (OUT), IC1.9 (-IN), X1.P$3 (CH2)
A3: IC1.13 (-IN), IC1.14 (OUT), X1.P$4 (CH3)
A4: IC2.1 (OUT), IC2.2 (-IN), X1.P$5 (CH4)
A5: IC2.6 (-IN), IC2.7 (OUT), X1.P$6 (CH5)
A6: IC2.8 (OUT), IC2.9 (-IN), X1.P$7 (CH6)
A7: IC2.13 (-IN), IC2.14 (OUT), X1.P$8 (CH7)
CLK: SENSOR_FRC.1, X1.P$13 (CLK)
CS: SENSOR_FRC.2, X1.P$10 (!CS)
GND: IC1.11 (V-), IC2.11 (V-), LED0.K (C), LED1.K (C), LED2.K (C), LED3.K (C), LED4.K (C), LED5.K (C), LED6.K (C), LED7.K (C), S0.1, S1.1, S2.1, S3.1, S4.1, S5.1, S6.1, S7.1, SENSOR_FRC.6, SENSOR_FRC.8, SENSOR_FRC.10, X1.P$9 (DGND), X1.P$14 (AGND)
MISO: SENSOR_FRC.4, X1.P$12 (DOUT)
MOSI: SENSOR_FRC.3, X1.P$11 (DIN)
unnamed: LED0.A, R0.1
unnamed: LED1.A, R1.1
unnamed: LED2.A, R2.1
unnamed: LED3.A, R3.1
unnamed: LED4.A, R4.1
unnamed: LED5.A, R5.1
unnamed: LED6.A, R6.1
unnamed: LED7.A, R7.1
unnamed: D1.A, IC1.5 (+IN), S1.2
unnamed: D2.A, IC1.10 (+IN), S2.2
unnamed: D3.A, IC1.12 (+IN), S3.2
unnamed: D4.A, IC2.3 (+IN), S4.2
unnamed: D5.A, IC2.5 (+IN), S5.2
unnamed: D6.A, IC2.10 (+IN), S6.2
unnamed: D7.A, IC2.12 (+IN), S7.2
unnamed: D0.A, IC1.3 (+IN), S0.2
VCC: D0.K (C), D1.K (C), D2.K (C), D3.K (C), D4.K (C), D5.K (C), D6.K (C), D7.K (C), IC1.4 (V+), IC2.4 (V+), R0.2, R1.2, R2.2, R3.2, R4.2, R5.2, R6.2, R7.2, SENSOR_FRC.5, SENSOR_FRC.7, SENSOR_FRC.9, X1.P$15 (VREF), X1.P$16 (VDD)

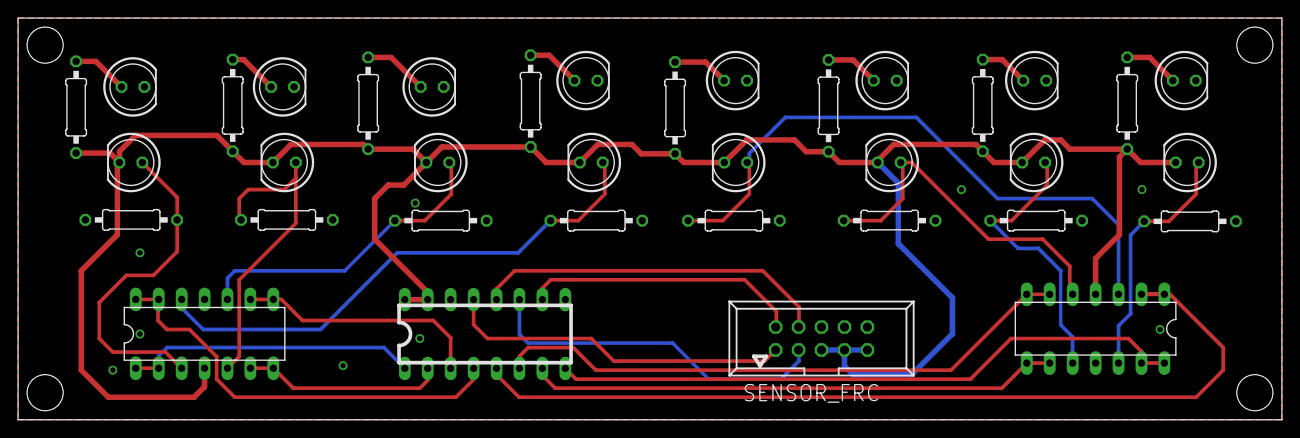
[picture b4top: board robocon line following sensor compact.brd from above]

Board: 2 copper layers, 140.0 x 44.5 mm, 36 parts (0 on the bottom side), 30 nets.

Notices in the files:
parts and their libraries:
Wurth_Elektronik_Electromechanic_Switch_: Copyright: Würth Elektronik
